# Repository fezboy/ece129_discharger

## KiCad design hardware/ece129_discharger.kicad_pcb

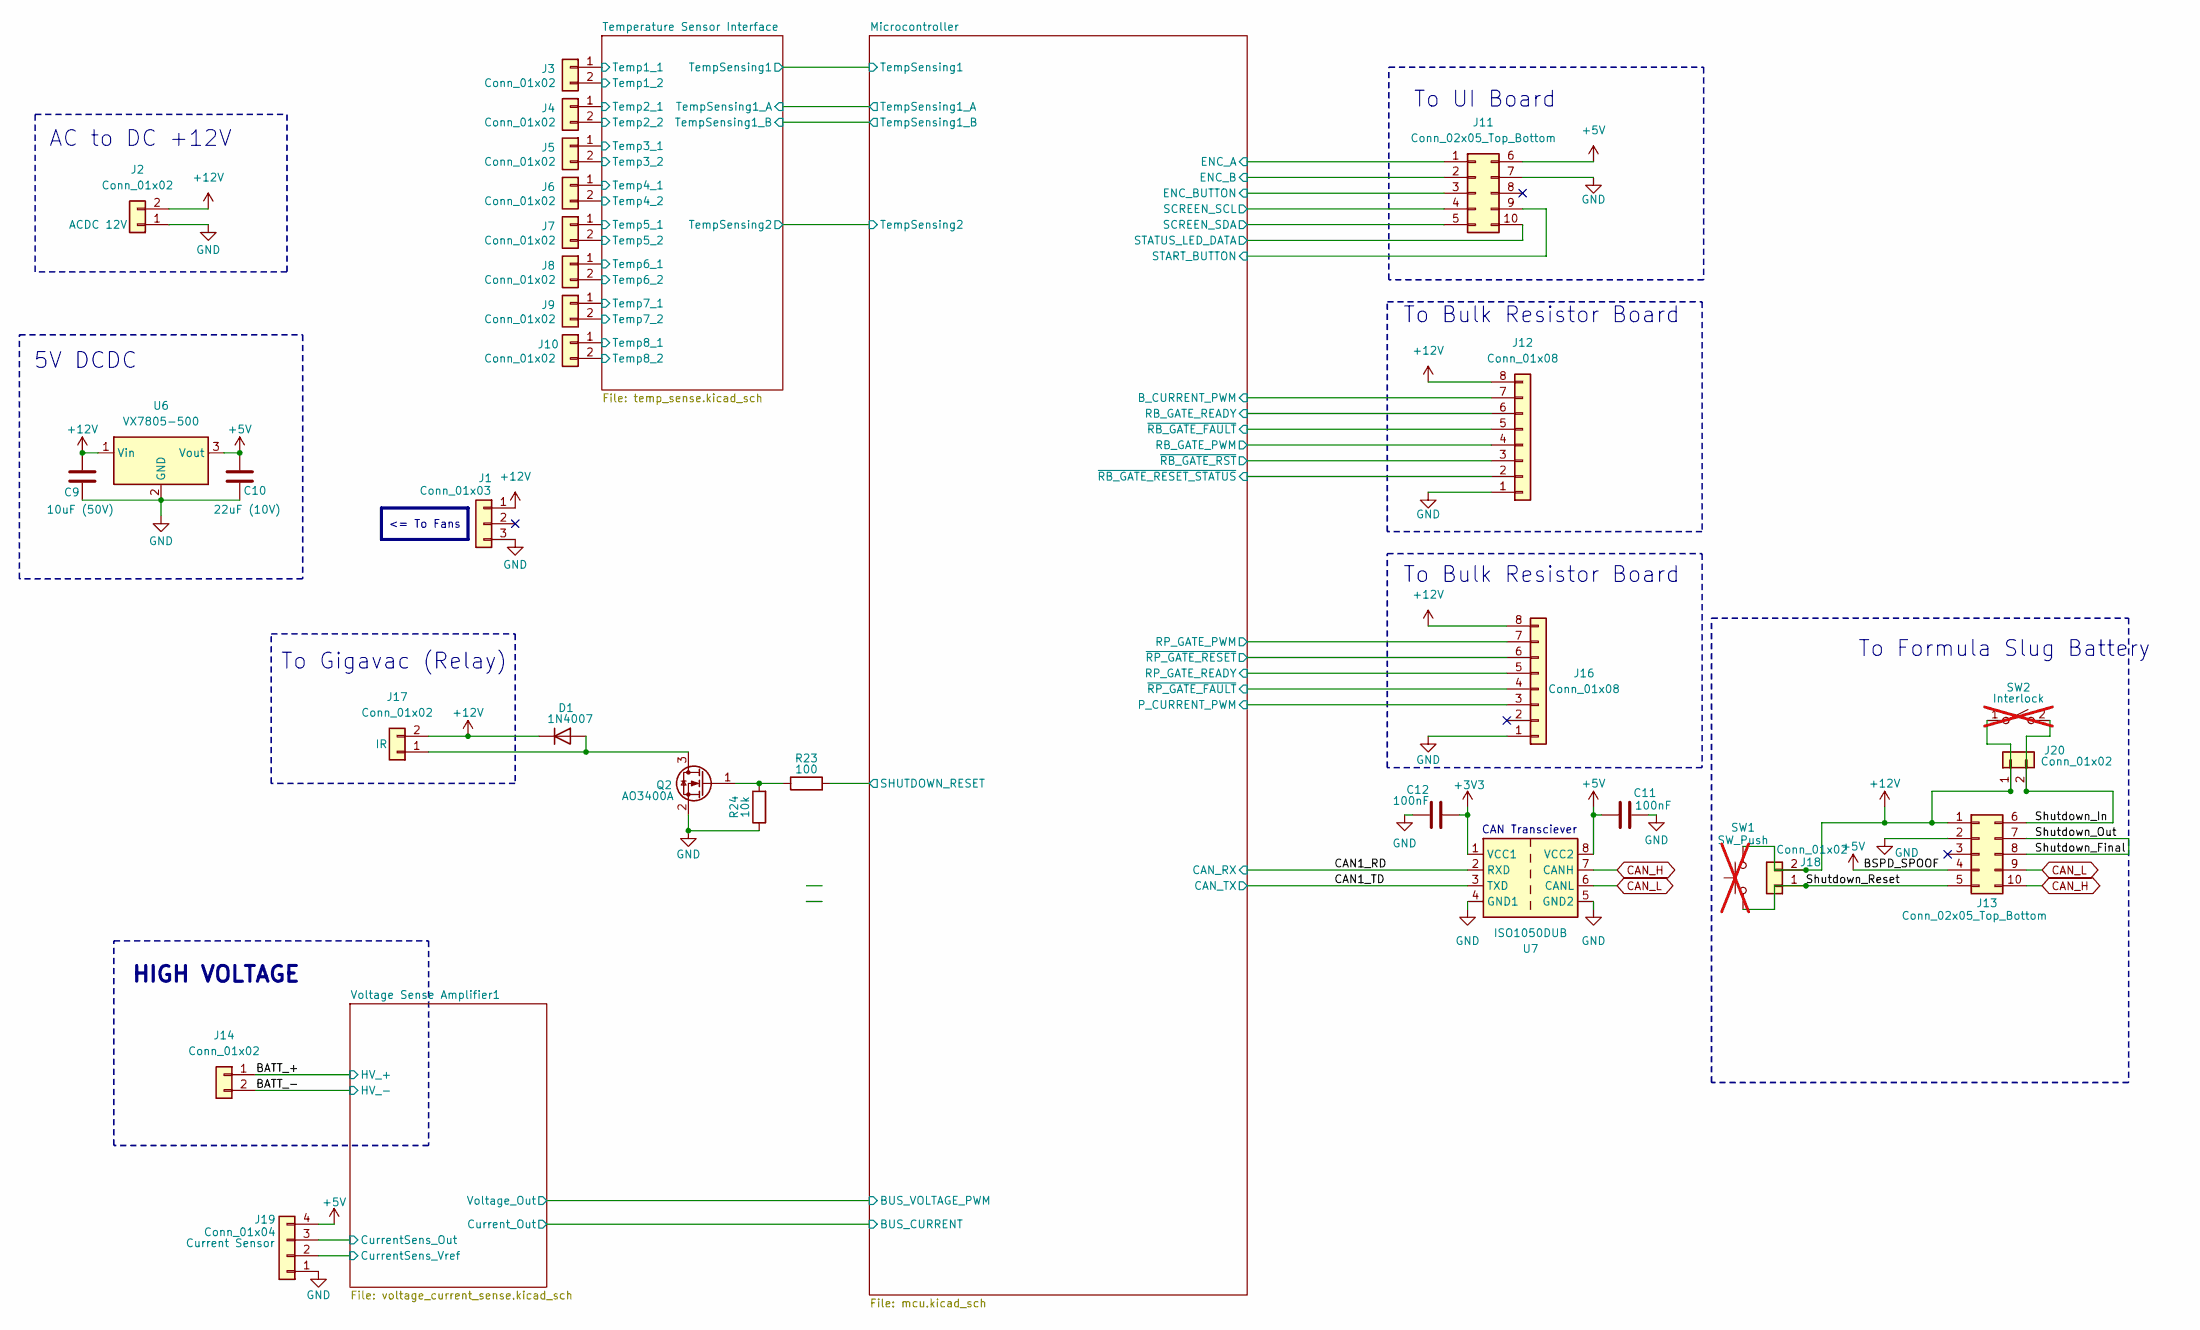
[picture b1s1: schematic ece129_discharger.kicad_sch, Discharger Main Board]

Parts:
C9: 10uF (50V); C_0805_2012Metric_Pad1.18x1.45mm_HandSolder
C10: 22uF (10V); C_0805_2012Metric_Pad1.18x1.45mm_HandSolder
C11, C12: 100nF; C_0805_2012Metric_Pad1.18x1.45mm_HandSolder
D1: 1N4007; D_DO-41_SOD81_P10.16mm_Horizontal
J1: Conn_01x03; Molex_Nano-Fit_105309-xx03_1x03_P2.50mm_Vertical
J2, J3, J4, J5, J6, J7, J8, J9, J10, J14, J17, J18, J20: Conn_01x02; Molex_Nano-Fit_105309-xx02_1x02_P2.50mm_Vertical
J11, J13: Conn_02x05_Top_Bottom; Molex_Nano-Fit_105310-xx10_2x05_P2.50mm_Vertical
J12, J16: Conn_01x08; Molex_Nano-Fit_105309-xx08_1x08_P2.50mm_Vertical
J19: Conn_01x04; Molex_Nano-Fit_105309-xx04_1x04_P2.50mm_Vertical
Q2: AO3400A; SOT-23
R23: 100; R_0805_2012Metric_Pad1.20x1.40mm_HandSolder
R24: 10k; R_0805_2012Metric_Pad1.20x1.40mm_HandSolder
SW1: SW_Push; not fitted
SW2: Interlock; not fitted
U6: VX7805-500; Converter_DCDC_TRACO_TSR0.5-24xx_TSR0.5-24xxx_THT
U7: ISO1050DUB; SOP-8_6.62x9.15mm_P2.54mm

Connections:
+3V3: C12.2, U7.1 (VCC1); also elsewhere on the board
+5V: C10.1, C11.2, J11.6, J13.4, J19.4, U6.3 (Vout), U7.8 (VCC2); also elsewhere on the board
+12V: C9.1, D1.1 (K), J1.1, J2.2, J12.8, J13.1, J16.8, J17.2, J18.2, J20.1, SW1.1, SW2.1 (A), U6.1 (Vin); also elsewhere on the board
/BATT_+: J14.1; also elsewhere on the board
/CAN1_RD: U7.2 (RXD); also elsewhere on the board
/CAN1_TD: U7.3 (TXD); also elsewhere on the board
/Microcontroller/B_CURRENT_PWM: J12.7; also elsewhere on the board
/Microcontroller/ENC_A: J11.1; also elsewhere on the board
/Microcontroller/ENC_B: J11.2; also elsewhere on the board
/Microcontroller/ENC_BUTTON: J11.3; also elsewhere on the board
/Microcontroller/P_CURRENT_PWM: J16.3; also elsewhere on the board
/Microcontroller/RB_GATE_PWM: J12.4; also elsewhere on the board
/Microcontroller/RB_GATE_READY: J12.6; also elsewhere on the board
/Microcontroller/RP_GATE_PWM: J16.7; also elsewhere on the board
/Microcontroller/RP_GATE_READY: J16.5; also elsewhere on the board
/Microcontroller/SCREEN_SCL: J11.4; also elsewhere on the board
/Microcontroller/SCREEN_SDA: J11.5; also elsewhere on the board
/Microcontroller/SHUTDOWN_RESET: R23.2; also elsewhere on the board
/Microcontroller/START_BUTTON: J11.9; also elsewhere on the board
/Microcontroller/STATUS_LED_DATA: J11.10; also elsewhere on the board
/Microcontroller/~RB_GATE_FAULT: J12.5; also elsewhere on the board
/Microcontroller/~RB_GATE_RESET_STATUS: J12.2; also elsewhere on the board
/Microcontroller/~RB_GATE_RST: J12.3; also elsewhere on the board
/Microcontroller/~RP_GATE_FAULT: J16.4; also elsewhere on the board
/Microcontroller/~RP_GATE_RESET: J16.6; also elsewhere on the board
/Shutdown_Final: J13.7, J13.8
/Shutdown_In: J13.6, J20.2, SW2.2 (B)
/Shutdown_Reset: J13.5, J18.1, SW1.2
/Temperature Sensor Interface/Temp1_1: J3.1; also elsewhere on the board
/Temperature Sensor Interface/Temp2_1: J4.1; also elsewhere on the board
/Temperature Sensor Interface/Temp3_1: J5.1; also elsewhere on the board
/Temperature Sensor Interface/Temp4_1: J6.1; also elsewhere on the board
/Temperature Sensor Interface/Temp5_1: J7.1; also elsewhere on the board
/Temperature Sensor Interface/Temp6_1: J8.1; also elsewhere on the board
/Temperature Sensor Interface/Temp7_1: J9.1; also elsewhere on the board
/Temperature Sensor Interface/Temp8_1: J10.1; also elsewhere on the board
/Voltage Sense Amplifier1/CurrentSens_Out: J19.3; also elsewhere on the board
/Voltage Sense Amplifier1/CurrentSens_Vref: J19.2; also elsewhere on the board
CAN_H: J13.10, U7.7 (CANH)
CAN_L: J13.9, U7.6 (CANL)
GND: C9.2, C10.2, C11.1, C12.1, J1.3, J2.1, J3.2, J4.2, J5.2, J6.2, J7.2, J8.2, J9.2, J10.2, J11.7, J12.1, J13.2, J16.1, J19.1, Q2.2 (S), R24.1, U6.2 (GND), U7.4 (GND1), U7.5 (GND2); also elsewhere on the board
HV_-: J14.2; also elsewhere on the board
unnamed: D1.2 (A), J17.1, Q2.3 (D)
unnamed: Q2.1 (G), R23.1, R24.2

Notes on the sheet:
CAN Transciever
AC to DC +12V
5V DCDC
To Bulk Resistor Board
HIGH VOLTAGE
To UI Board
To Formula Slug Battery
To Gigavac (Relay)
<= To Fans

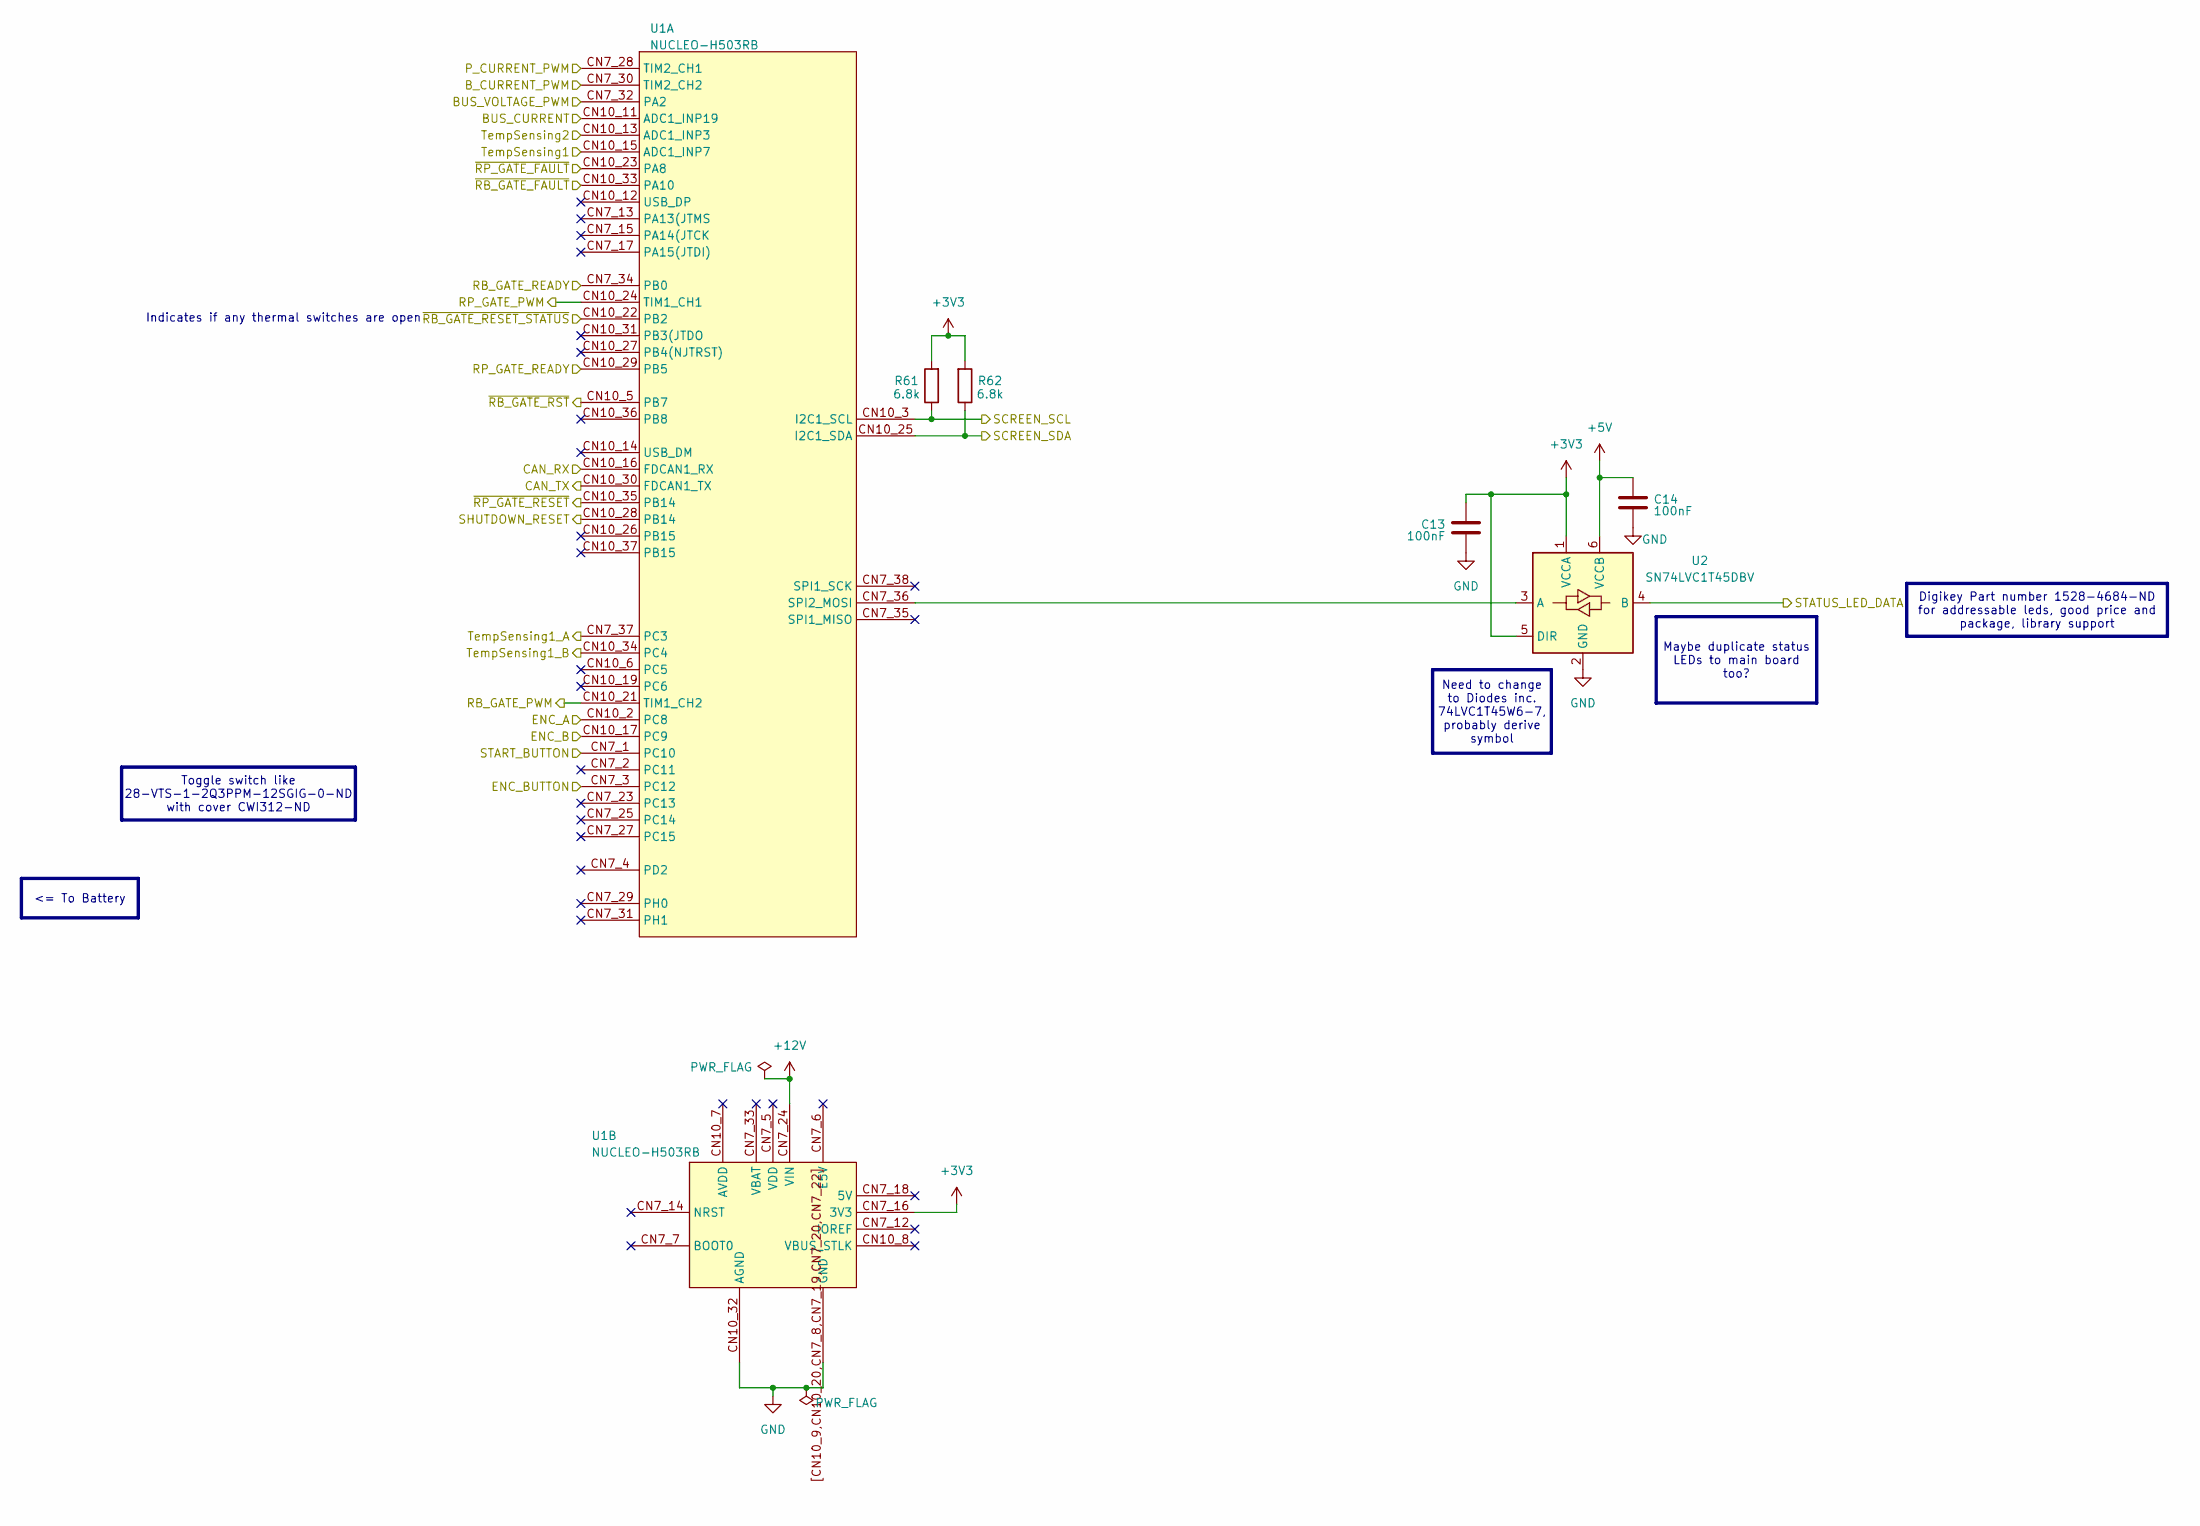
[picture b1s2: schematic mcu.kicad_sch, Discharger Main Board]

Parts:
C13, C14: 100nF; C_0805_2012Metric_Pad1.18x1.45mm_HandSolder
R61, R62: 6.8k; R_0805_2012Metric_Pad1.20x1.40mm_HandSolder
U1: NUCLEO-H503RB
U2: SN74LVC1T45DBV; SOT-23-6

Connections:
+3V3: C13.1, R61.2, R62.2, U1.CN7_16 (3V3), U2.1 (VCCA), U2.5 (DIR); also elsewhere on the board
+5V: C14.1, U2.6 (VCCB); also elsewhere on the board
+12V: U1.CN7_24 (VIN); also elsewhere on the board
/CAN1_RD: U1.CN10_16 (FDCAN1_RX); also elsewhere on the board
/CAN1_TD: U1.CN10_30 (FDCAN1_TX); also elsewhere on the board
/Microcontroller/BUS_CURRENT: U1.CN10_11 (ADC1_INP19); also elsewhere on the board
/Microcontroller/BUS_VOLTAGE_PWM: U1.CN7_32 (PA2); also elsewhere on the board
/Microcontroller/B_CURRENT_PWM: U1.CN7_30 (TIM2_CH2); also elsewhere on the board
/Microcontroller/ENC_A: U1.CN10_2 (PC8); also elsewhere on the board
/Microcontroller/ENC_B: U1.CN10_17 (PC9); also elsewhere on the board
/Microcontroller/ENC_BUTTON: U1.CN7_3 (PC12); also elsewhere on the board
/Microcontroller/P_CURRENT_PWM: U1.CN7_28 (TIM2_CH1); also elsewhere on the board
/Microcontroller/RB_GATE_PWM: U1.CN10_21 (TIM1_CH2); also elsewhere on the board
/Microcontroller/RB_GATE_READY: U1.CN7_34 (PB0); also elsewhere on the board
/Microcontroller/RP_GATE_PWM: U1.CN10_24 (TIM1_CH1); also elsewhere on the board
/Microcontroller/RP_GATE_READY: U1.CN10_29 (PB5); also elsewhere on the board
/Microcontroller/SCREEN_SCL: R61.1, U1.CN10_3 (I2C1_SCL); also elsewhere on the board
/Microcontroller/SCREEN_SDA: R62.1, U1.CN10_25 (I2C1_SDA); also elsewhere on the board
/Microcontroller/SHUTDOWN_RESET: U1.CN10_28 (PB14); also elsewhere on the board
/Microcontroller/START_BUTTON: U1.CN7_1 (PC10); also elsewhere on the board
/Microcontroller/STATUS_LED_DATA: U2.4 (B); also elsewhere on the board
/Microcontroller/TempSensing1: U1.CN10_15 (ADC1_INP7); also elsewhere on the board
/Microcontroller/TempSensing1_A: U1.CN7_37 (PC3); also elsewhere on the board
/Microcontroller/TempSensing1_B: U1.CN10_34 (PC4); also elsewhere on the board
/Microcontroller/TempSensing2: U1.CN10_13 (ADC1_INP3); also elsewhere on the board
/Microcontroller/~RB_GATE_FAULT: U1.CN10_33 (PA10); also elsewhere on the board
/Microcontroller/~RB_GATE_RESET_STATUS: U1.CN10_22 (PB2); also elsewhere on the board
/Microcontroller/~RB_GATE_RST: U1.CN10_5 (PB7); also elsewhere on the board
/Microcontroller/~RP_GATE_FAULT: U1.CN10_23 (PA8); also elsewhere on the board
/Microcontroller/~RP_GATE_RESET: U1.CN10_35 (PB14); also elsewhere on the board
GND: C13.2, C14.2, U1.CN7_8 (GND), U1.CN7_19 (GND), U1.CN7_20 (GND), U1.CN7_22 (GND), U1.CN10_9 (GND), U1.CN10_20 (GND), U1.CN10_32 (AGND), U1.[CN10_9,CN10_20,CN7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 (GND), U2.2 (GND); also elsewhere on the board
unnamed: U1.CN7_36 (SPI2_MOSI), U2.3 (A)

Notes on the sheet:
Indicates if any thermal switches are open
Digikey Part number 1528-4684-ND for addressable leds, good price and package, library support
Toggle switch like 28-VTS-1-2Q3PPM-12SGIG-0-ND with cover CWI312-ND
Need to change to Diodes inc. 74LVC1T45W6-7, probably derive symbol
Maybe duplicate status LEDs to main board too?
<= To Battery

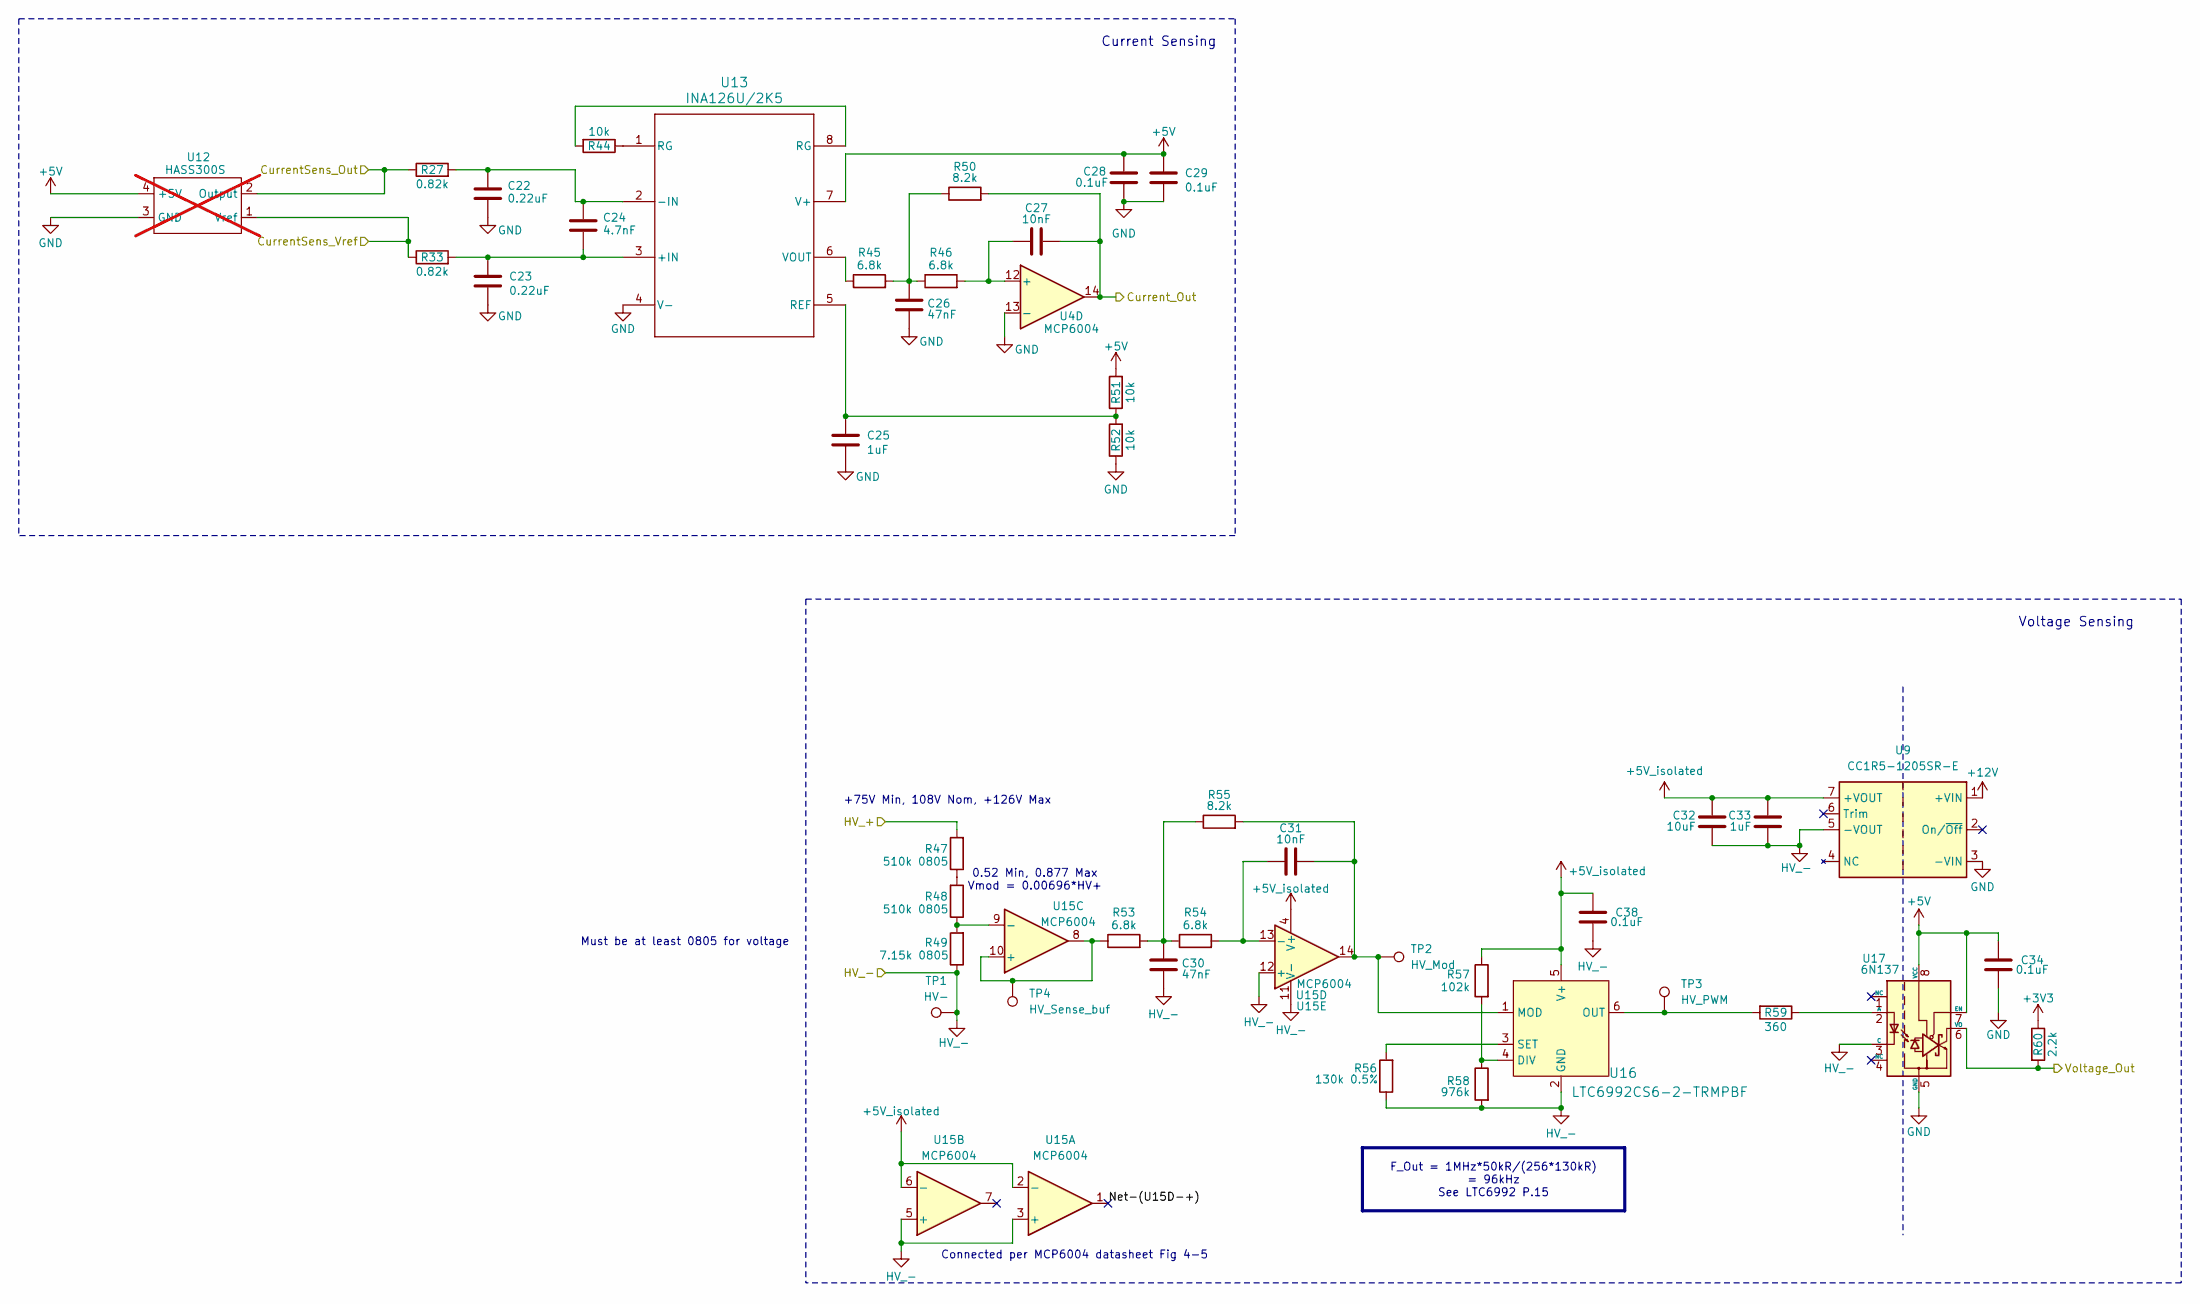
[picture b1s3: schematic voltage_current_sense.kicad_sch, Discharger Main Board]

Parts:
C22, C23: 0.22uF; C_0805_2012Metric_Pad1.18x1.45mm_HandSolder
C24: 4.7nF; C_0805_2012Metric_Pad1.18x1.45mm_HandSolder
C25, C33: 1uF; C_0805_2012Metric_Pad1.18x1.45mm_HandSolder
C26, C30: 47nF; C_0805_2012Metric_Pad1.18x1.45mm_HandSolder
C27, C31: 10nF; C_0805_2012Metric_Pad1.18x1.45mm_HandSolder
C28, C29, C34, C38: 0.1uF; C_0805_2012Metric_Pad1.18x1.45mm_HandSolder
C32: 10uF; C_0805_2012Metric_Pad1.18x1.45mm_HandSolder
R27, R33: 0.82k; R_0805_2012Metric_Pad1.20x1.40mm_HandSolder
R44, R51, R52: 10k; R_0805_2012Metric_Pad1.20x1.40mm_HandSolder
R45, R46, R53, R54: 6.8k; R_0805_2012Metric_Pad1.20x1.40mm_HandSolder
R47, R48: 510k 0805; R_0805_2012Metric_Pad1.20x1.40mm_HandSolder
R49: 7.15k 0805; R_0805_2012Metric_Pad1.20x1.40mm_HandSolder
R50, R55: 8.2k; R_0805_2012Metric_Pad1.20x1.40mm_HandSolder
R56: 130k 0.5%; R_0805_2012Metric_Pad1.20x1.40mm_HandSolder
R57: 102k; R_0805_2012Metric_Pad1.20x1.40mm_HandSolder
R58: 976k; R_0805_2012Metric_Pad1.20x1.40mm_HandSolder
R59: 360; R_0805_2012Metric_Pad1.20x1.40mm_HandSolder
R60: 2.2k; R_0805_2012Metric_Pad1.20x1.40mm_HandSolder
TP1: HV-; TestPoint_Keystone_5015_Micro_Mini
TP2: HV_Mod; TestPoint_Keystone_5015_Micro_Mini
TP3: HV_PWM; TestPoint_Keystone_5015_Micro_Mini
TP4: HV_Sense_buf; TestPoint_Keystone_5015_Micro_Mini
U4, U15: MCP6004; SOIC-14_3.9x8.7mm_P1.27mm
U9: CC1R5-1205SR-E; MFG PN CC1R5-1205SR-E; Digi PN 445-2453-ND
U12: HASS300S; not fitted
U13: INA126U/2K5; SOIC-8_5.3x6.2mm_P1.27mm
U16: LTC6992CS6-2-TRMPBF; TSOT-23-6; MFG PN LTC6992CS6-2-TRMPBF; Digi PN 505-LTC6992CS6-2#TRMPBFCT-ND
U17: 6N137; DIP-8_W7.62mm

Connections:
+3V3: R60.1; also elsewhere on the board
+5V: C28.1, C29.1, C34.1, R51.2, U12.4 (+5V), U13.7 (V+), U17.7 (EN), U17.8 (VCC); also elsewhere on the board
+5V_isolated: C32.1, C33.1, C38.1, R57.1, U9.7 (+VOUT), U15.2 (-), U15.4 (V+), U15.6 (-), U16.5 (V+)
+12V: U9.1 (+VIN); also elsewhere on the board
/BATT_+: R47.2; also elsewhere on the board
/Microcontroller/BUS_CURRENT: C27.2, R50.2, U4.14; also elsewhere on the board
/Microcontroller/BUS_VOLTAGE_PWM: R60.2, U17.6 (VO); also elsewhere on the board
/Voltage Sense Amplifier1/CurrentSens_Out: R27.1, U12.2 (Output); also elsewhere on the board
/Voltage Sense Amplifier1/CurrentSens_Vref: R33.1, U12.1 (Vref); also elsewhere on the board
/Voltage Sense Amplifier1/Net-(U15D-+): U15.1
GND: C22.2, C23.2, C25.2, C26.1, C28.2, C29.2, C34.2, R52.1, U4.13 (-), U9.3 (-VIN), U12.3 (GND), U13.4 (V-), U17.5 (GND); also elsewhere on the board
HV_-: C30.1, C32.2, C33.2, C38.2, R49.1, R56.1, R58.2, TP1.1 (1_1), U9.5 (-VOUT), U15.3 (+), U15.5 (+), U15.11 (V-), U15.12 (+), U16.2 (GND), U17.3 (C); also elsewhere on the board
unnamed: C26.2, R45.2, R46.1, R50.1
unnamed: C30.2, R53.2, R54.1, R55.1
unnamed: R44.1, U13.1 (RG)
unnamed: R44.2, U13.8 (RG)
unnamed: R47.1, R48.2
unnamed: C27.1, R46.2, U4.12 (+)
unnamed: C23.1, C24.2, R33.2, U13.3 (+IN)
unnamed: C22.1, C24.1, R27.2, U13.2 (-IN)
unnamed: C25.1, R51.1, R52.2, U13.5 (REF)
unnamed: R45.1, U13.6 (VOUT)
unnamed: R53.1, TP4.1 (1_1), U15.8, U15.10 (+)
unnamed: R48.1, R49.2, U15.9 (-)
unnamed: C31.1, R54.2, U15.13 (-)
unnamed: R57.2, R58.1, U16.4 (DIV)
unnamed: C31.2, R55.2, TP2.1 (1_1), U15.14, U16.1 (MOD)
unnamed: R59.2, TP3.1 (1_1), U16.6 (OUT)
unnamed: R56.2, U16.3 (SET)
unnamed: R59.1, U17.2 (A)

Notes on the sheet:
+75V Min, 108V Nom, +126V Max
0.52 Min, 0.877 Max Vmod = 0.00696*HV+
Connected per MCP6004 datasheet Fig 4-5
Voltage Sensing
Must be at least 0805 for voltage
Current Sensing
F_Out = 1MHz*50kR/(256*130kR) = 96kHz See LTC6992 P.15

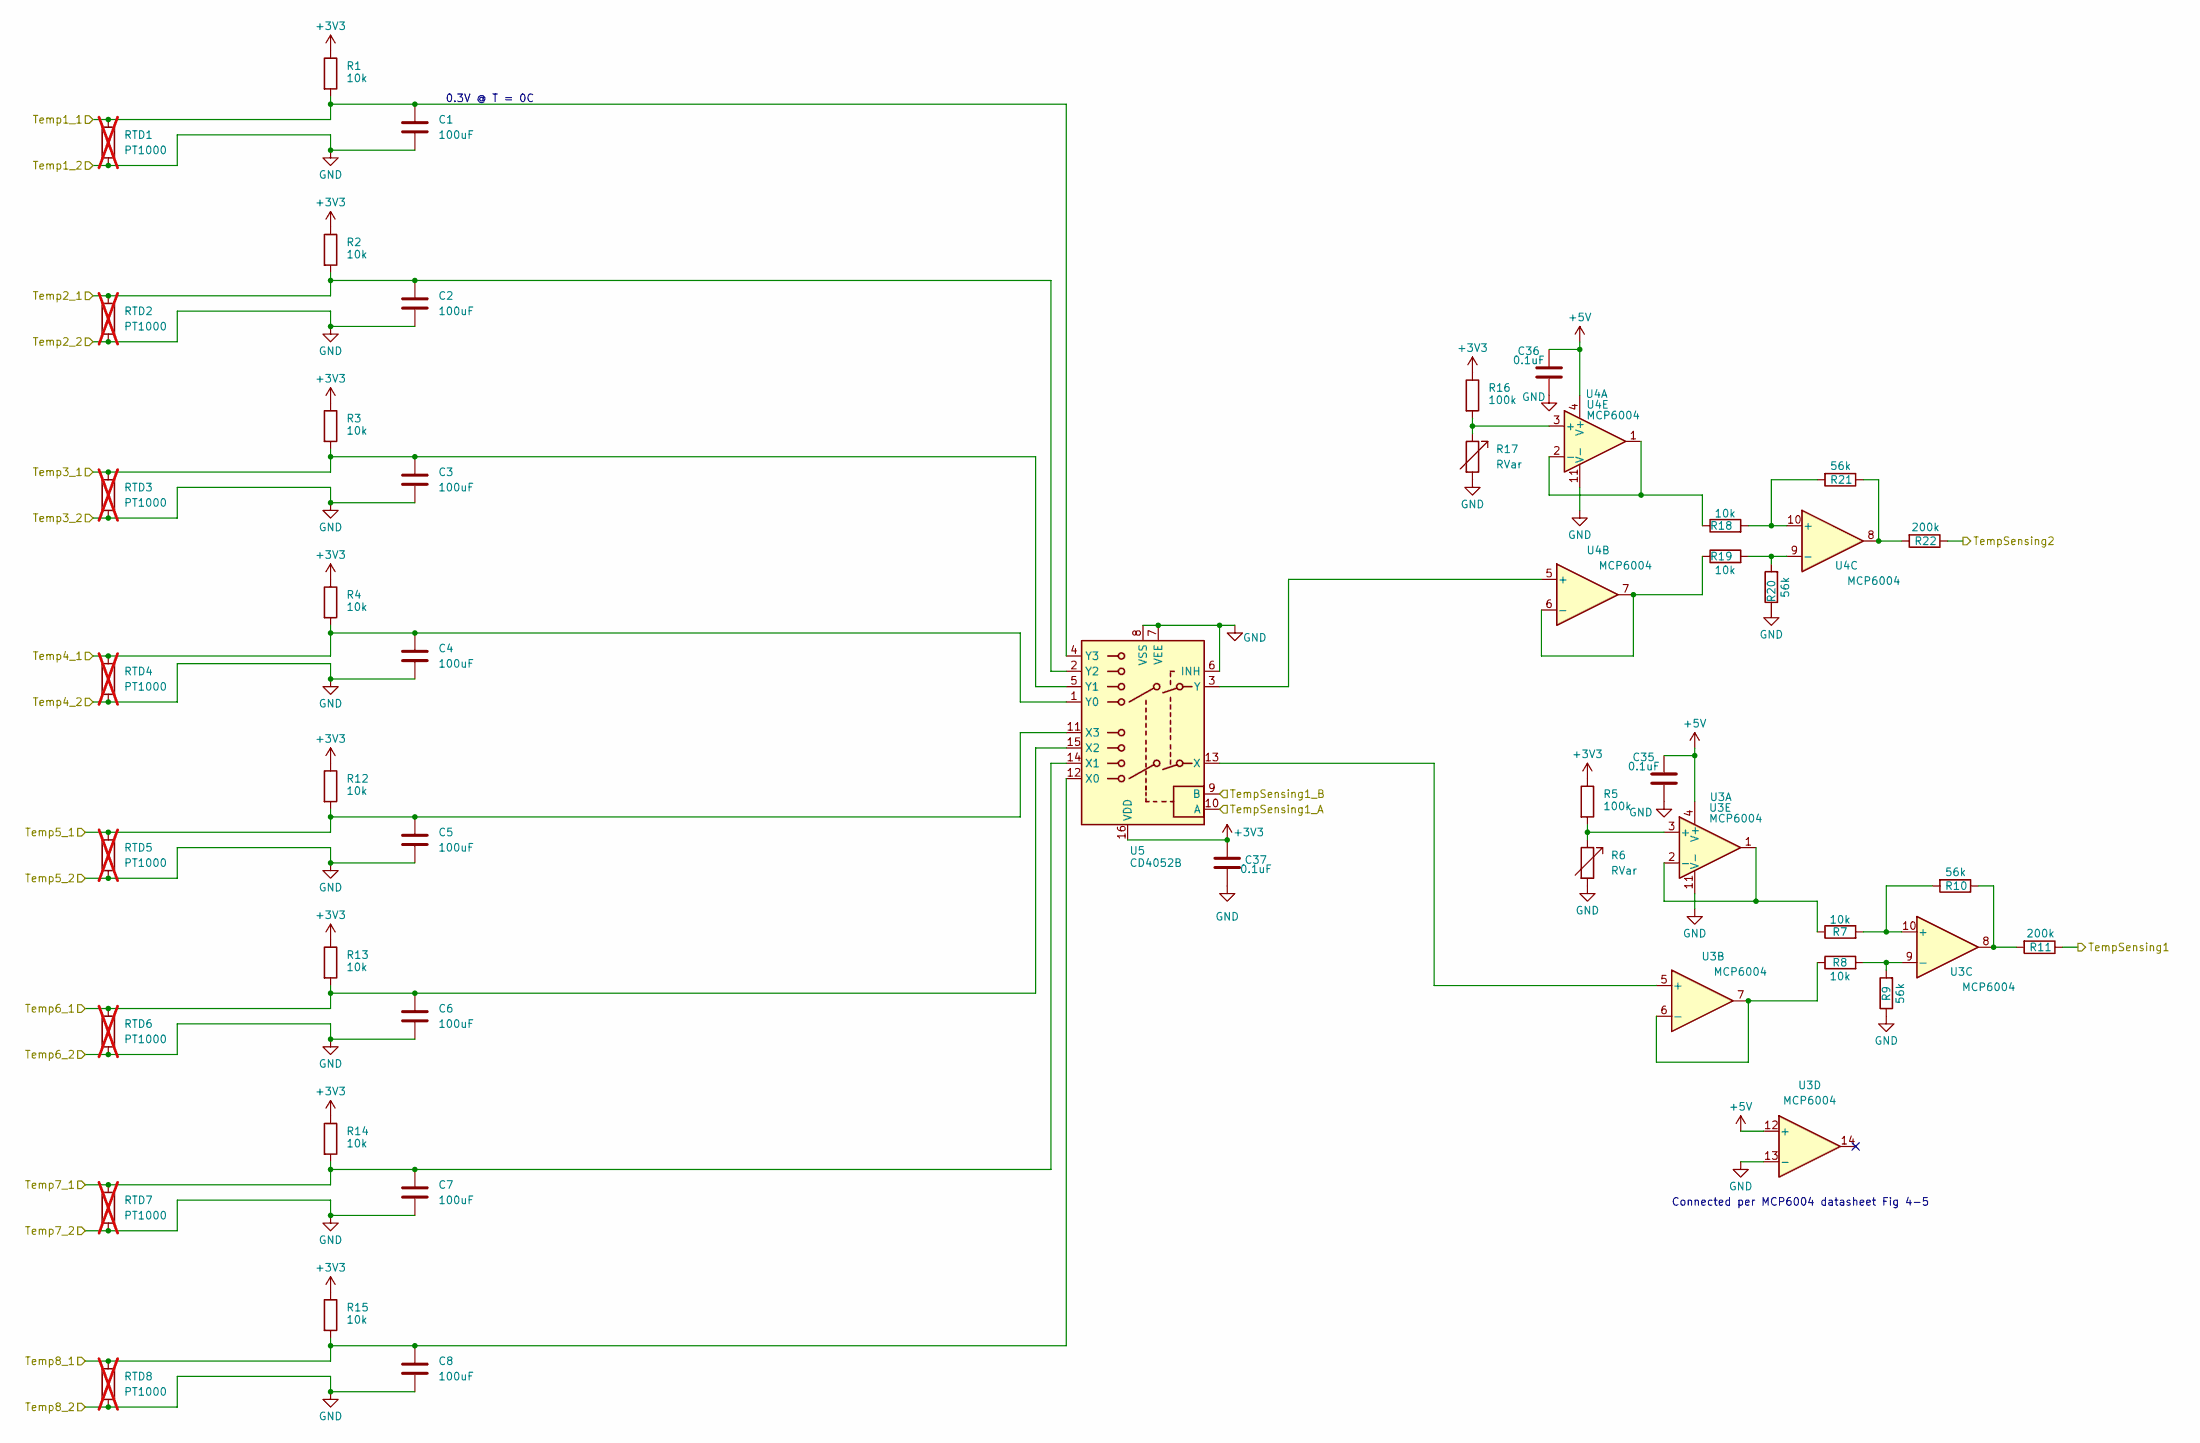
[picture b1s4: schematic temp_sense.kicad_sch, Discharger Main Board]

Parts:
C1, C2, C3, C4, C5, C6, C7, C8: 100uF; C_0805_2012Metric_Pad1.18x1.45mm_HandSolder
C35, C36, C37: 0.1uF; C_0805_2012Metric_Pad1.18x1.45mm_HandSolder
R1, R2, R3, R4, R7, R8, R12, R13, R14, R15, R18, R19: 10k; R_0805_2012Metric_Pad1.20x1.40mm_HandSolder
R5, R16: 100k; R_0805_2012Metric_Pad1.20x1.40mm_HandSolder
R6, R17: RVar; Potentiometer_Bourns_3296W_Vertical
R9, R10, R20, R21: 56k; R_0805_2012Metric_Pad1.20x1.40mm_HandSolder
R11, R22: 200k; R_0805_2012Metric_Pad1.20x1.40mm_HandSolder
RTD1, RTD2, RTD3, RTD4, RTD5, RTD6, RTD7, RTD8: PT1000; not fitted
U3, U4: MCP6004; SOIC-14_3.9x8.7mm_P1.27mm
U5: CD4052B; TSSOP-16_4.4x5mm_P0.65mm

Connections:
+3V3: C37.1, R1.1, R2.1, R3.1, R4.1, R5.1, R12.1, R13.1, R14.1, R15.1, R16.1, U5.16 (VDD); also elsewhere on the board
+5V: C35.1, C36.1, U3.4 (V+), U3.12 (+), U4.4 (V+); also elsewhere on the board
/Microcontroller/TempSensing1: R11.1; also elsewhere on the board
/Microcontroller/TempSensing1_A: U5.10 (A); also elsewhere on the board
/Microcontroller/TempSensing1_B: U5.9 (B); also elsewhere on the board
/Microcontroller/TempSensing2: R22.1; also elsewhere on the board
/Temperature Sensor Interface/Temp1_1: C1.1, R1.2, RTD1.1, U5.4 (Y3); also elsewhere on the board
/Temperature Sensor Interface/Temp2_1: C2.1, R2.2, RTD2.1, U5.2 (Y2); also elsewhere on the board
/Temperature Sensor Interface/Temp3_1: C3.1, R3.2, RTD3.1, U5.5 (Y1); also elsewhere on the board
/Temperature Sensor Interface/Temp4_1: C4.1, R4.2, RTD4.1, U5.1 (Y0); also elsewhere on the board
/Temperature Sensor Interface/Temp5_1: C5.1, R12.2, RTD5.1, U5.11 (X3); also elsewhere on the board
/Temperature Sensor Interface/Temp6_1: C6.1, R13.2, RTD6.1, U5.15 (X2); also elsewhere on the board
/Temperature Sensor Interface/Temp7_1: C7.1, R14.2, RTD7.1, U5.14 (X1); also elsewhere on the board
/Temperature Sensor Interface/Temp8_1: C8.1, R15.2, RTD8.1, U5.12 (X0); also elsewhere on the board
GND: C1.2, C2.2, C3.2, C4.2, C5.2, C6.2, C7.2, C8.2, C35.2, C36.2, C37.2, R6.2, R9.1, R17.2, R20.1, RTD1.2, RTD2.2, RTD3.2, RTD4.2, RTD5.2, RTD6.2, RTD7.2, RTD8.2, U3.11 (V-), U3.13 (-), U4.11 (V-), U5.6 (INH), U5.7 (VEE), U5.8 (VSS); also elsewhere on the board
unnamed: R10.1, R11.2, U3.8
unnamed: R21.1, R22.2, U4.8
unnamed: R5.2, R6.1, U3.3 (+)
unnamed: R7.1, U3.1, U3.2 (-)
unnamed: U3.5 (+), U5.13 (X)
unnamed: R8.1, U3.6 (-), U3.7
unnamed: R7.2, R10.2, U3.10 (+)
unnamed: R8.2, R9.2, U3.9 (-)
unnamed: R16.2, R17.1, U4.3 (+)
unnamed: R18.1, U4.1, U4.2 (-)
unnamed: U4.5 (+), U5.3 (Y)
unnamed: R19.1, U4.6 (-), U4.7
unnamed: R18.2, R21.2, U4.10 (+)
unnamed: R19.2, R20.2, U4.9 (-)

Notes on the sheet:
0.3V @ T = 0C
Connected per MCP6004 datasheet Fig 4-5

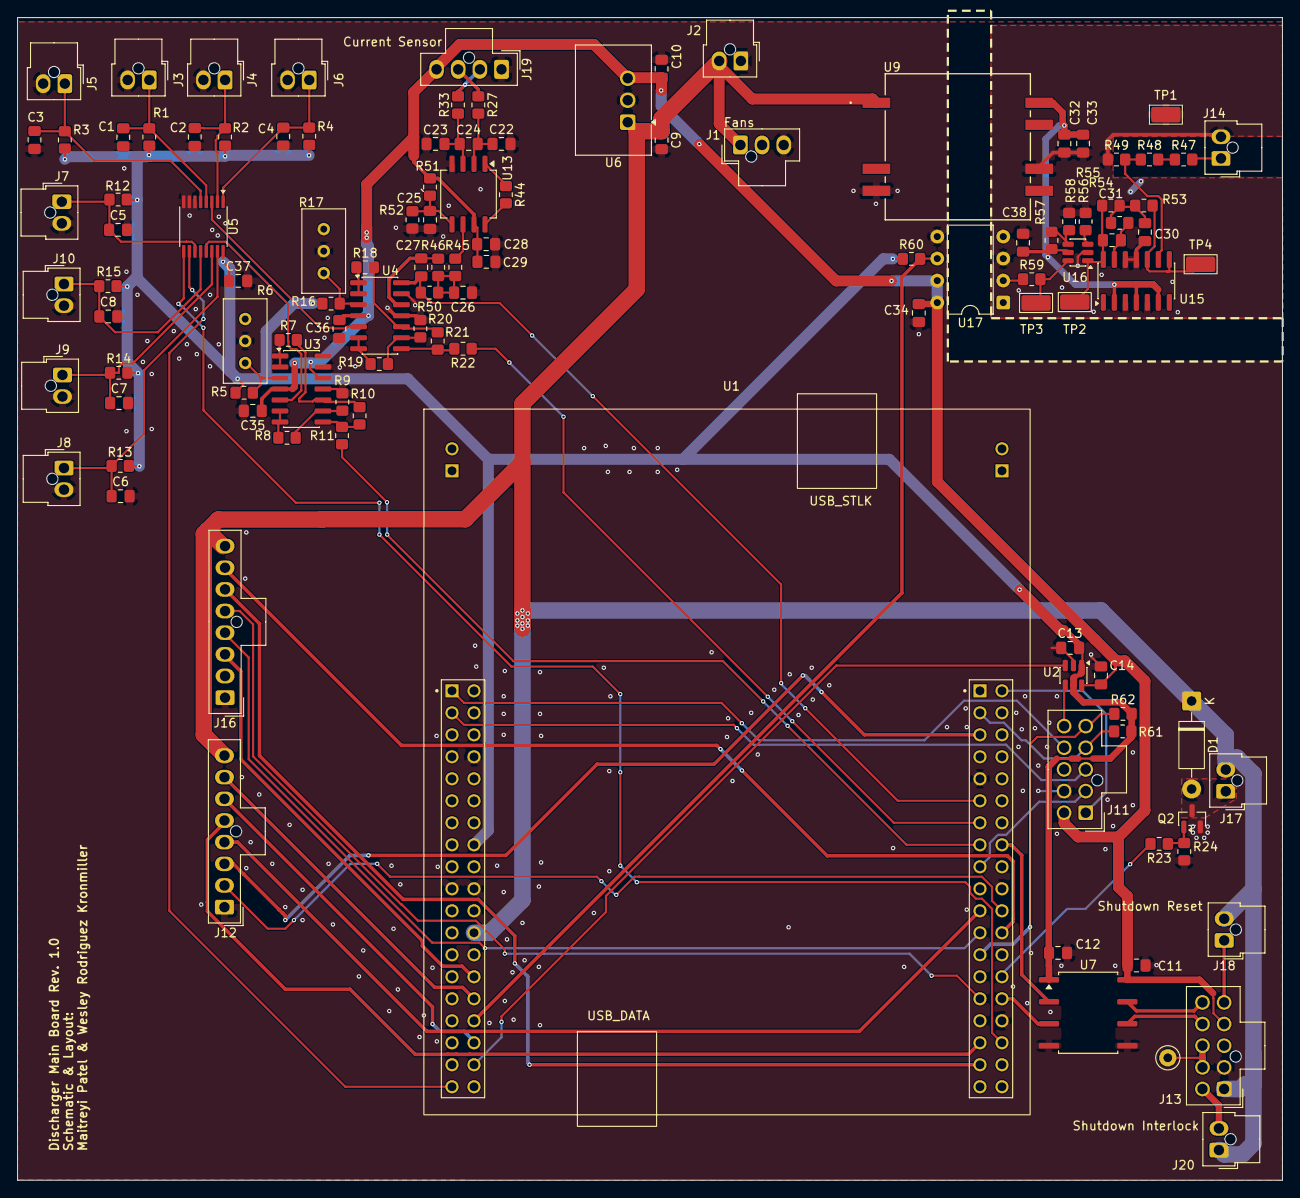
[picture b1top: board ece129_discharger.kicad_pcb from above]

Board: 2 copper layers, 146.0 x 134.2 mm, 113 parts (0 on the bottom side), 84 nets.
